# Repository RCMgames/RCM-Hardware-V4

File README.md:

# RCM-Hardware-V4

v1.3

* 4 motors and 7 servos OR 6 motors and 3 servos
* 3 additional input only pins
* 2 x 3 inches, 50.8 x 76.2 mm
* runs from 5 NiMH AA batteries OR 4.5-12v with the addition of voltage regulators (see list of components)
* [Qwiic](https://www.sparkfun.com/qwiic#faqs) connectors OR two more GPIO pins
* all components are hand-solderable through-hole parts except for the Qwiic connectors which are surface mount

Compatible with 38 pin devkitC ESP32 boards

program with [RCMv2](https://github.com/RCMgames/RCMv2)

### Alternatives
* An upgrade from [the original 3 versions of RCM boards](https://github.com/RCMgames/RCM_hardware_documentation_and_user_guide)

* Here are smaller and more powerful RCM boards: [BYTE](https://github.com/RCMgames/RCM-Hardware-BYTE) and [Nibble](https://github.com/RCMgames/RCM-Hardware-Nibble)

## Options for purchasing

* [PCBWay link](https://www.pcbway.com/project/shareproject/W454600ASI60_gerbers_RCM_Hardware_V4_v1_3_38d50617.html) (PCBWay will give me a commission without increasing the price for you). (approximately $5 for 5 boards and manufacturing takes 1-7 days).
* send the gerbers to a PCB manufacturer of your choice (details you may be asked for: min hole: 0.3mm, min track/spacing 6/6mil, 1 oz Cu outer)

## Components
Solder by hand to assemble your boards.
| part | links | quantity | notes |
| ----- | ----- | ----- | ----- |
| RCM V4 circuit board | see options for purchasing above | 1 | |
| ESP32 devkitC 38 pin | [digikey](https://www.digikey.com/en/products/detail/espressif-systems/ESP32-DEVKITC-32E/12091810) or find on Amazon | 1 | |
| L293D (or SN754410) | [digikey](https://www.digikey.com/en/products/detail/texas-instruments/L293DNE/379724) | 2 or 3 | |
| 16 pin IC socket | | 0 to 3 | depending on whether you solder the ICs directly and how many motors you want to use |
| 30k resistor | | 1 | |
| 10k resistor | | 1 | |
| 47uF capacitor | | 1 | |
| Qwiic connector (JST SH) | [digikey](https://www.digikey.com/en/products/detail/jst-sales-america-inc/SM04B-SRSS-TB/926710) | 0 to 2 | |
| 4 male header pins | | 1 | for I2C pins |
| 5 male header pins | | 1 | for extra input pins |
| 7 male header pins | | 4 | for servos |
| 4 female header pins | | 3 | for motors (can also use one 12 pin strip instead) |
| 19 female header pins | | 2 | for esp32 |
| battery wires | 2 male header pins OR JST RCY OR 9V battery snap | 1 | [Amazon JST RCY](https://www.amazon.com/dp/B00Z04QFN2/) |
| servo buck boost 5v 2A | [Pololu](https://www.pololu.com/product/4085) | 0 or 1 | if you want to supply voltages above or below what servos can accept (supplies other than 5AAs) |
| esp32 buck 5v 0.6A | [Pololu](https://www.pololu.com/product/3792) | 0 or 1 | if you want to supply voltages above 7 volts (supplies other than 5AAs) |

The six pins at the bottom of the board near the QWIIC connectors are not connected to anything. They are meant to be used for soldering practice before adding components that matter.

## Acknowledgements
* I would like to thank [PCBWay](https://www.pcbway.com/) for sponsoring prototyping runs of this project. PCBWay produces very nice boards, supports open source hardware, and gave me great support as I worked on this project. Special thanks to Liam!

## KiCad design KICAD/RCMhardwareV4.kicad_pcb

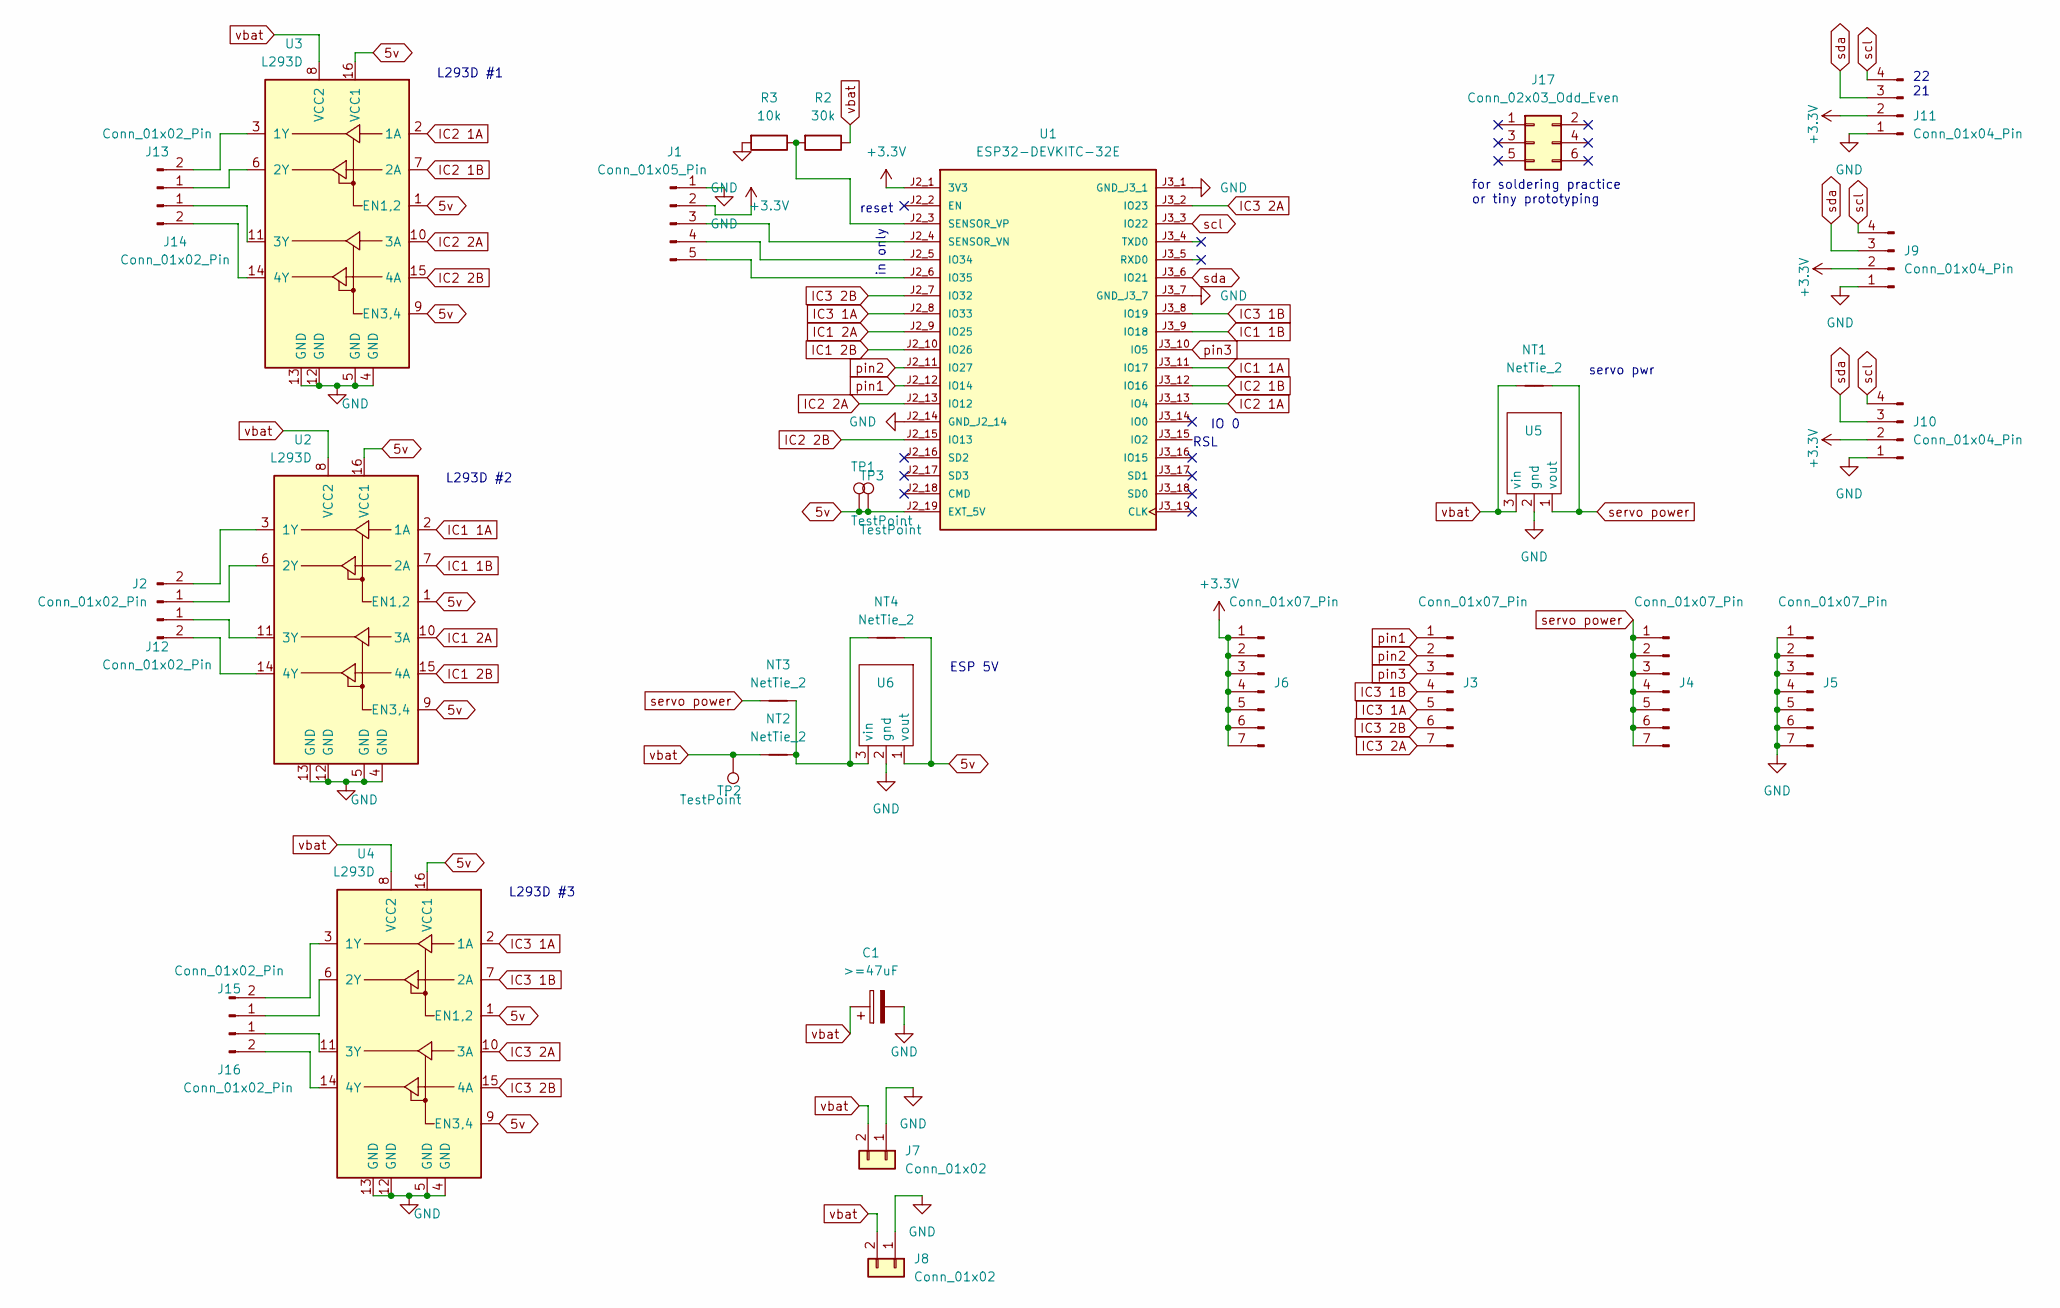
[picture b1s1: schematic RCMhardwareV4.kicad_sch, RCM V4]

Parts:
C1: >=47uF; C_Radial_D8.0mm_H11.5mm_P3.50mm
J1: Conn_01x05_Pin; PinHeader_1x05_P2.54mm_Vertical
J2, J12, J13, J14, J15, J16: Conn_01x02_Pin; PinSocket_1x02_P2.54mm_Vertical
J3, J4, J5, J6: Conn_01x07_Pin; PinHeader_1x07_P2.54mm_Vertical
J7: Conn_01x02; battery wires
J8: Conn_01x02; PinHeader_1x02_P2.54mm_Vertical
J9, J10: Conn_01x04_Pin; JST_SH_SM04B-SRSS-TB_1x04-1MP_P1.00mm_Horizontal
J11: Conn_01x04_Pin; PinHeader_1x04_P2.54mm_Vertical
J17: Conn_02x03_Odd_Even; PinHeader_2x03_P2.54mm_Vertical
NT1: NetTie_2; SolderJumper-2_P1.3mm_Bridged2Bar_RoundedPad1.0x1.5mm
NT2, NT4: NetTie_2; SolderJumper-2_P1.3mm_Bridged_RoundedPad1.0x1.5mm
NT3: NetTie_2; SolderJumper-2_P1.3mm_Open_RoundedPad1.0x1.5mm
R2: 30k; R_Axial_DIN0207_L6.3mm_D2.5mm_P10.16mm_Horizontal
R3: 10k; R_Axial_DIN0207_L6.3mm_D2.5mm_P10.16mm_Horizontal
TP1, TP2, TP3: TestPoint; TestPoint_THTPad_D2.0mm_Drill1.0mm
U1: ESP32-DEVKITC-32E; MODULE_ESP32-DEVKITC-32E
U2, U3, U4: L293D; DIP-16_W7.62mm_Socket
U5: pololu4085
U6: pololu3792

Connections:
5v: NT4.2, TP1.1, TP3.1, U1.J2_19 (EXT_5V), U2.1 (EN1,2), U2.9 (EN3,4), U2.16 (VCC1), U3.1 (EN1,2), U3.9 (EN3,4), U3.16 (VCC1), U4.1 (EN1,2), U4.9 (EN3,4), U4.16 (VCC1), U6.1 (vout)
+3.3V: J1.2, J6.1, J6.2, J6.3, J6.4, J6.5, J6.6, J6.7, J9.2, J10.2, J11.2, U1.J2_1 (3V3)
GND: C1.2, J1.1, J5.1, J5.2, J5.3, J5.4, J5.5, J5.6, J5.7, J7.1, J8.1, J9.1, J10.1, J11.1, R3.2, U1.J2_14 (GND_J2_14), U1.J3_1 (GND_J3_1), U1.J3_7 (GND_J3_7), U2.4 (GND), U2.5 (GND), U2.12 (GND), U2.13 (GND), U3.4 (GND), U3.5 (GND), U3.12 (GND), U3.13 (GND), U4.4 (GND), U4.5 (GND), U4.12 (GND), U4.13 (GND), U5.2 (gnd), U6.2 (gnd)
IC1 1A: U1.J3_11 (IO17), U2.2 (1A)
IC1 1B: U1.J3_9 (IO18), U2.7 (2A)
IC1 2A: U1.J2_9 (IO25), U2.10 (3A)
IC1 2B: U1.J2_10 (IO26), U2.15 (4A)
IC2 1A: U1.J3_13 (IO4), U3.2 (1A)
IC2 1B: U1.J3_12 (IO16), U3.7 (2A)
IC2 2A: U1.J2_13 (IO12), U3.10 (3A)
IC2 2B: U1.J2_15 (IO13), U3.15 (4A)
IC3 1A: J3.5, U1.J2_8 (IO33), U4.2 (1A)
IC3 1B: J3.4, U1.J3_8 (IO19), U4.7 (2A)
IC3 2A: J3.7, U1.J3_2 (IO23), U4.10 (3A)
IC3 2B: J3.6, U1.J2_7 (IO32), U4.15 (4A)
unnamed: J1.3, U1.J2_4 (SENSOR_VN)
unnamed: J1.4, U1.J2_5 (IO34)
unnamed: J1.5, U1.J2_6 (IO35)
unnamed: J2.1, U2.6 (2Y)
unnamed: J2.2, U2.3 (1Y)
unnamed: J12.1, U2.11 (3Y)
unnamed: J12.2, U2.14 (4Y)
unnamed: J13.1, U3.6 (2Y)
unnamed: J13.2, U3.3 (1Y)
unnamed: J14.1, U3.11 (3Y)
unnamed: J14.2, U3.14 (4Y)
unnamed: J15.1, U4.6 (2Y)
unnamed: J15.2, U4.3 (1Y)
unnamed: J16.1, U4.11 (3Y)
unnamed: J16.2, U4.14 (4Y)
unnamed: R2.2, R3.1, U1.J2_3 (SENSOR_VP)
unnamed: NT2.2, NT3.2, NT4.1, U6.3 (vin)
pin1: J3.1, U1.J2_12 (IO14)
pin2: J3.2, U1.J2_11 (IO27)
pin3: J3.3, U1.J3_10 (IO5)
scl: J9.4, J10.4, J11.4, U1.J3_3 (IO22)
sda: J9.3, J10.3, J11.3, U1.J3_6 (IO21)
servo power: J4.1, J4.2, J4.3, J4.4, J4.5, J4.6, J4.7, NT1.2, NT3.1, U5.1 (vout)
vbat: C1.1, J7.2, J8.2, NT1.1, NT2.1, R2.1, TP2.1, U2.8 (VCC2), U3.8 (VCC2), U4.8 (VCC2), U5.3 (vin)

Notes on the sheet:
in only
L293D #3
servo pwr
for soldering practice or tiny prototyping
RSL
L293D #2
22 21
ESP 5V
reset
L293D #1
IO 0

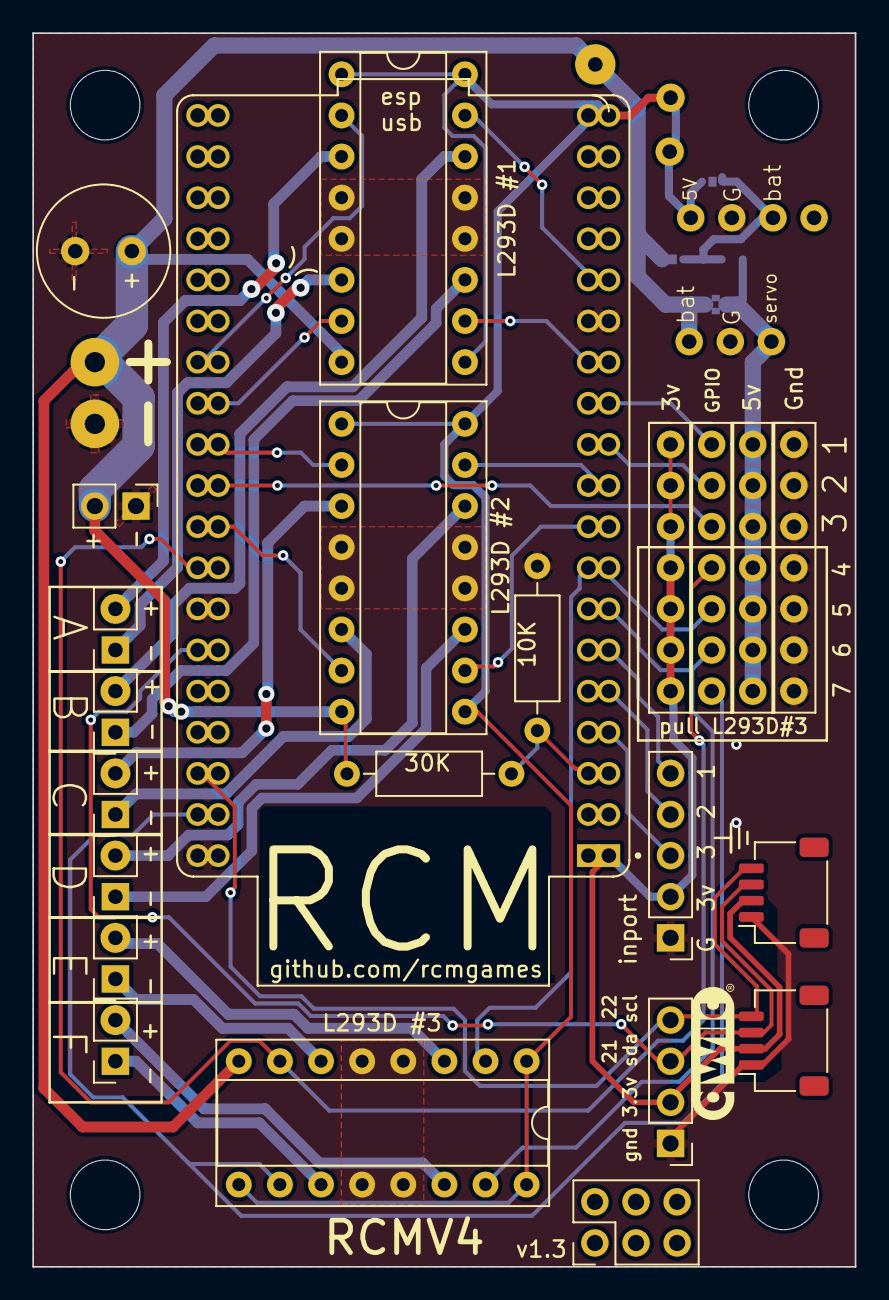
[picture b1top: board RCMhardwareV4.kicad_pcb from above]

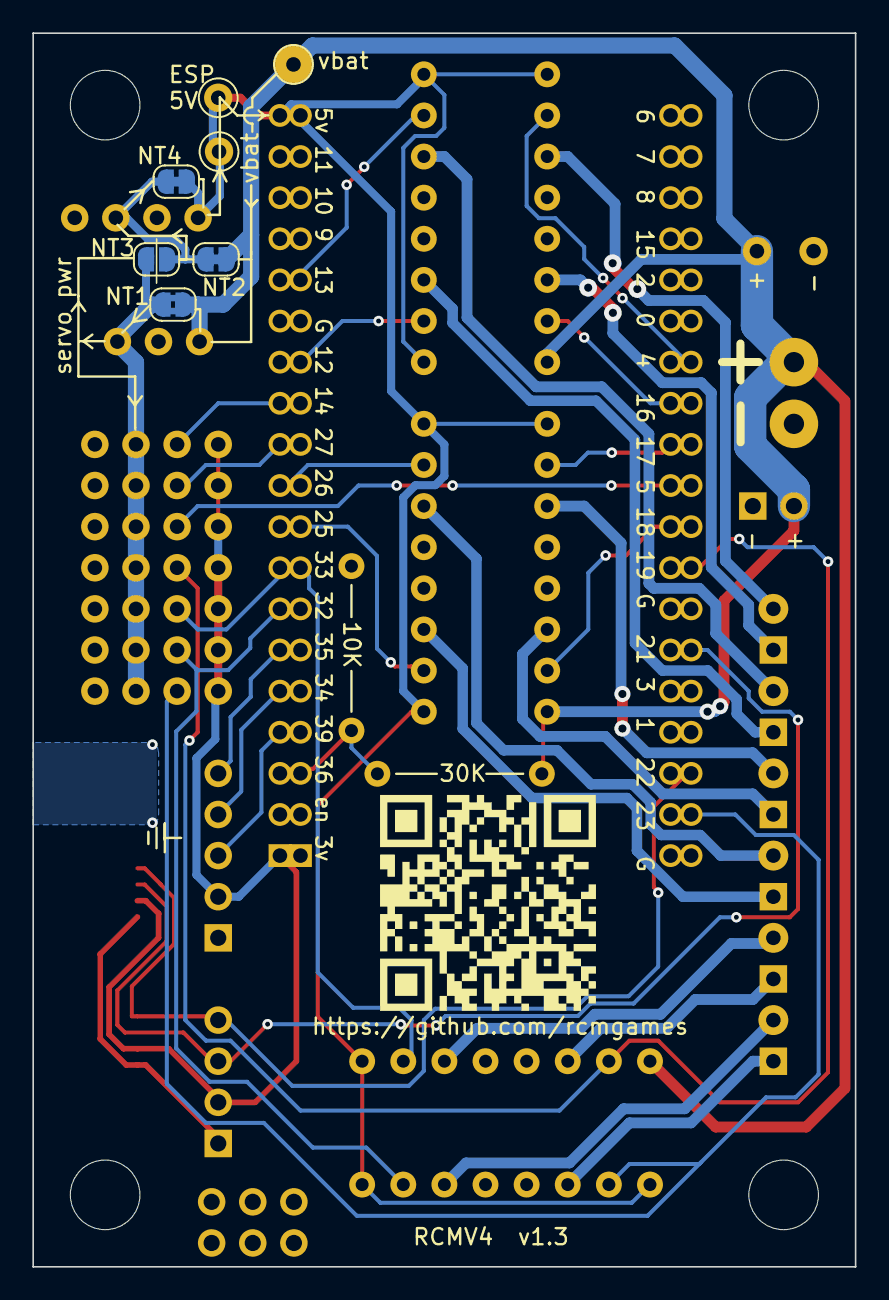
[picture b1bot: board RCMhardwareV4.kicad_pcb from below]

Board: 2 copper layers, 50.8 x 76.2 mm, 37 parts (7 on the bottom side), 39 nets.

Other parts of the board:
H1, H2, H3, H4: MountingHole; MountingHole_4.3mm_M4

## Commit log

2024-04-18 v4.0.0
2024-04-25 v1.1.1
2024-04-25 add cad render
2024-04-25 Rename gerbers.zip to gerbers-RCM-Hardware-V4-v1.1.zip
2024-05-04 v1.2 close #3 #4 #5
2024-05-04 rename
2024-05-27 v1.3
2024-05-27 update screenshots
2024-06-07 add pictures
2025-01-12 Update README.md to mention that SN754410 chips can be used to replace L293D chips
